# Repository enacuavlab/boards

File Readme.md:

# ENAC boards

This repository contains various resources related to ENAC's UAV team electronic boards, like hardware source files, and software templates.

## Tawaki

This is the lastest autopilot board based on a STMicroelectronics STM32F777VI.

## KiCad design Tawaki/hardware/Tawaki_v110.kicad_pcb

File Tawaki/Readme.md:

# Tawaki

This is the lastest autopilot board based on a STMicroelectronics STM32F777VI.

Find more details in the [Paparazzi UAV wiki](http://wiki.paparazziuav.org/wiki/Tawaki/v1.10).

+ **tawaki_chibios**: ChibiOS 20.3 basic example for Tawaki
+ **hardware**: electronic schematics and board KiCad files

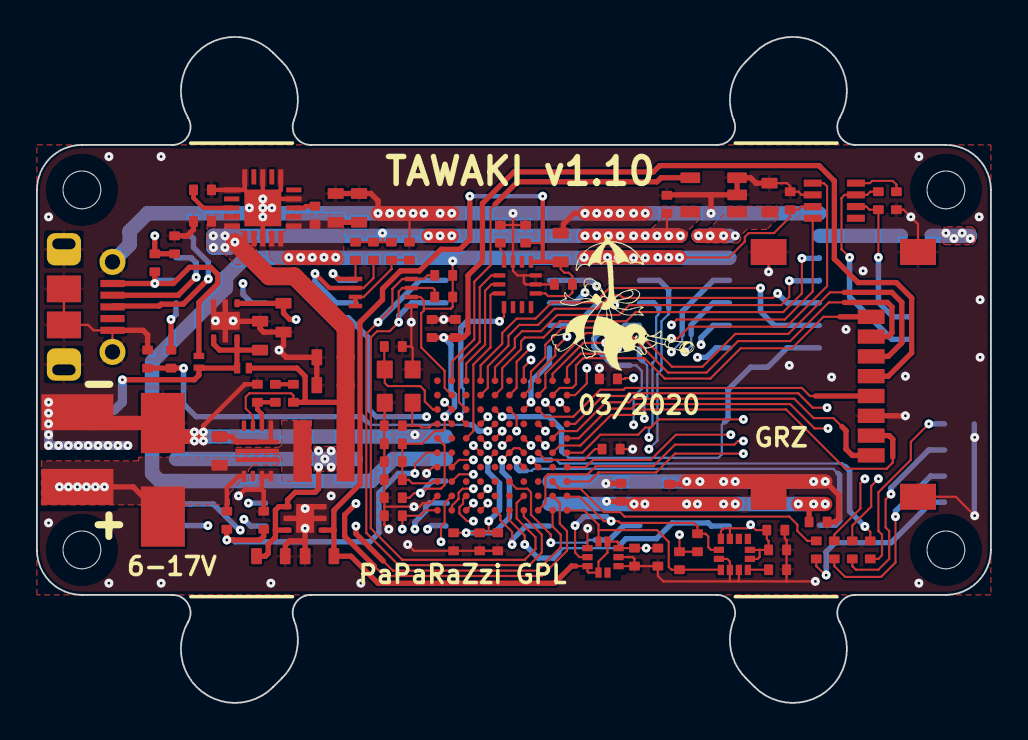
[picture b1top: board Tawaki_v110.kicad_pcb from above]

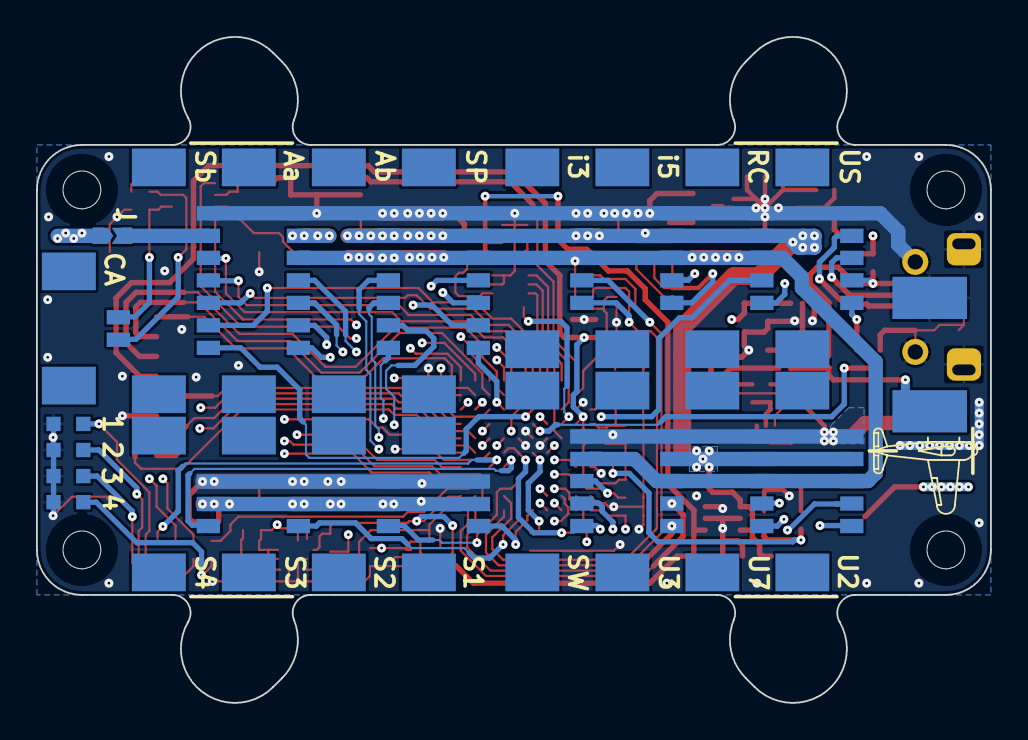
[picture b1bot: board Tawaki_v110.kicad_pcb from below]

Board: 4 copper layers, 53.0 x 37.0 mm, 107 parts (23 on the bottom side), 90 nets.

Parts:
C1, C2: 18pF; C_0402
C3, C4, C5, C6: 10nF; C_0402
C7, C8, C9, C10, C11, C12, C13, C14, C15, C16, C17, C18, C19, C20, C21, C22, C23, C24: 100nF; C_0402
C25, C26, C27, C28: 1µF; C_0402
C29: 1µF/25V/X5R; C_0603
C30, C31, C32: 4.7µF; C_0402
C33, C34, C35, C36, C37, C38, C39, C40, C41, C42: 10µF; C_0603
C43: 100µF/20V; EIA_7343-31
C44: 1000µF/6.3V; EIA_7360-38
D1, D2: PMEG3010AESB
IC1: TPS621351
IC2, IC3: LP5912-3.3DRV; LP5912DRV
IC4: TPS7A84ARGR
IC5: STM32F777VI
IC6: ICM-20600
IC7: LIS3MDL
IC8: BMP388
IC9: MAX3051EKA
IC10: PCA9306DCU
IC11: TPS2001DDBV
J1: CAN; PicoBlade_53398-0271
J2: SRVa1; PicoBlade_53398-0371
J3: SRVa2; PicoBlade_53398-0371
J4: SRVa3; PicoBlade_53398-0371
J5: SRVa4; PicoBlade_53398-0371
J6: SWD; PicoBlade_53398-0571
J7: RC; PicoBlade_53398-0571
J8: I2C-3V3; PicoBlade_53398-0571
J9: I2C-5V; PicoBlade_53398-0571
J10: UART2; PicoBlade_53398-0571
J11: UART3; PicoBlade_53398-0571
J12: UART7; PicoBlade_53398-0571
J13: USB; PicoBlade_53398-0571
J14: SRVb; PicoBlade_53398-0771
J15: AUXa; PicoBlade_53398-0771
J16: AUXb; PicoBlade_53398-0771
J17: SPI; PicoBlade_53398-0771
J18: USB_Micro-B; USB_Micro-B_Molex_105017-0001
J19: MicroSD_Connector_500901-0801; MicroSD_500901-0801
J20: +BAT; SquareWirePad_SMD_2x4mm
J21: GND; SquareWirePad_SMD_2x4mm
JP1: SolderJumper_2P; SolderJumper_2P_TrianglePads_0603
L1: 1µH; XFL4020
LED1: KP-1608SURC
LED2: KP-1608SEC
LED3: KP-1608CGCK
LED4: KP-1608SYC
Q1: 8Z_16MHz; Crystal_8Z
R1: 0Ω; R_0402
R2: 120Ω; R_0402
R3, R4, R5, R6: 390Ω; R_0402
R7, R8, R9: 1.5kΩ; R_0402
R10, R11, R12, R13, R14, R15, R16, R17, R18, R19: 2.2kΩ; R_0402
R20, R21: 12kΩ; R_0402
R22: 220kΩ; R_0402

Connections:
+3V3: C5.1, C22.2, C37.1, C38.1, IC4.1, IC4.2, IC4.19, IC4.20, IC5.B2, IC9.3, IC10.2, J6.2, J7.3, J8.3, J9.3, J10.3, J11.3, J12.3, J15.3, J16.3, J17.3, R13.1, R14.1
+3V3MCU: C12.1, C13.2, C14.2, C15.2, C18.2, C19.2, C26.2, C27.1, C31.2, C35.1, IC3.1, IC5.D2, IC5.F4, IC5.F5, IC5.F6, IC5.F7, IC5.H1, IC5.K1, J19.4
+3V3SENS: C3.2, C10.2, C11.1, C17.1, C24.2, C28.1, C40.1, C41.1, IC2.1, IC6.5, IC6.8, IC7.5, IC7.6, IC7.9, IC7.10, IC8.1, IC8.5, IC8.6, IC8.10, R11.1, R12.1
+5V: C9.1, C16.1, C20.1, C21.1, C25.1, C33.1, C39.1, C42.1, D1.2, IC1.6, IC2.4, IC2.6, IC4.14, IC4.15, IC4.16, IC4.17, IC11.5, J2.2, J3.2, J4.2, J5.2, J7.2, J8.2, J9.2, J10.2, J11.2, J12.2, J16.2, J17.2, L1.2, R15.1, R16.1, R21.2, R22.1
+5VAUX: C36.1, IC11.1, J15.2
+5VMCU: C34.1, C44.1, D1.1, D2.1, IC3.4, IC3.6
/APSW: IC5.A2, IC11.4
/AUXa1: IC5.G2, J15.4
/AUXa2: IC5.H2, J15.5
/AUXa3: IC5.J2, J15.6
/AUXa4: IC5.K2, J15.7
/AUXb1: IC5.J3, J16.4
/AUXb2: IC5.K3, J16.5
/AUXb3: IC5.J4, J16.6
/AUXb4: IC5.K4, J16.7
/BOOT: J13.5, R8.2
/BOOT0: IC5.D5, R8.1, R17.1
/CANH: IC9.7, J1.2, R2.1
/CANL: IC9.6, J1.1, R2.2
/CANRX: IC5.D8, IC9.4
/CANTX: IC5.E8, IC9.1
/DSHTin: IC5.C5, J14.7
/FB: IC1.5, R7.2, R10.1
/LED1: IC5.G8, R3.1
/LED2: IC5.D10, R4.1
/LED3: IC5.E10, R5.1
/LED4: IC5.H9, R6.1
/MISO2: IC5.H10, J17.6
/MISO4: IC5.D3, IC6.1
/MOSI2: IC5.G10, J17.5
/MOSI4: IC5.E3, IC6.14
/NSS2: IC5.K8, J17.4
/NSS4: IC5.C3, IC6.12
/OSCI: C2.2, IC5.C1, Q1.3
/OSCO: C1.2, IC5.D1, Q1.1
/RC1: IC5.D4, J7.4
/RC2: IC5.F10, J7.5
/RX2: IC5.C6, J10.4
/RX3: IC5.J9, J11.4
/RX7: IC5.A7, J12.4
/SCK2: IC5.C7, J17.7
/SCK4: IC5.A3, IC6.13
/SCL2: IC5.J7, IC10.3, J8.5, R14.2
/SCL2_5: IC10.6, J9.5, R16.2
/SCL4: IC5.K10, IC7.1, IC8.2, R12.2
/SD1ck: IC5.C8, J19.5
/SD1cmd: IC5.B7, J19.3
/SD1d0: IC5.F9, J19.7
/SD1d1: IC5.E9, J19.8
/SD1d2: IC5.B9, J19.1
/SD1d3: IC5.B8, J19.2
/SDA2: IC5.K7, IC10.4, J8.4, R13.2
/SDA2_5: IC10.5, J9.4, R15.2
/SDA4: IC5.J10, IC7.11, IC8.4, R11.2
/SRVa1: IC5.K5, J2.3
/SRVa2: IC5.H6, J3.3
/SRVa3: IC5.K6, J4.3
/SRVa4: IC5.G7, J5.3
/SRVb1: IC5.B5, J14.3
/SRVb2: IC5.A5, J14.4
/SRVb3: IC5.B4, J14.5
/SRVb4: IC5.A4, J14.6
/SW: IC1.2, L1.1
/SWCLK: IC5.A9, J6.4
/SWDIO: IC5.A10, J6.5
/TX2: IC5.B6, J10.5
/TX3: IC5.K9, J11.5
/TX7: IC5.A8, J12.5
/USB+: IC5.B10, J13.2, J18.3
/USB-: IC5.C10, J13.3, J18.2
/USBvbus: D2.2, J13.4, J18.1, R9.2
/USBvbus_LV: IC5.C9, R9.1, R19.1
/VBATmeas: IC5.F1, R18.1, R20.2
/VCAP1: C30.1, IC5.F8
/VCAP2: C32.1, IC5.E7
/nRST: C8.1, IC5.E1, J6.3
GND: C1.1, C2.1, C3.1, C4.2, C6.2, C7.2, C8.2, C9.2, C10.1, C11.2, C12.2, C13.1, C14.1, C15.1, C16.2, C17.2, C18.1, C19.1, C20.2, C21.2, C22.1, C23.2, C24.1, C25.2, C26.1, C27.2, C28.2, C29.2, C30.2, C31.1, C32.2, C33.2, C34.2, C35.2, C36.2, C37.2, C38.2, C39.2, C40.2, C41.2, C42.2, C43.2, C44.2, IC1.3, IC1.4, IC1.10, IC1.11, IC2.2, IC2.3, IC2.5, IC2.7, IC3.2, IC3.3, IC3.5, IC3.7, IC4.4, IC4.6, IC4.8, IC4.10, IC4.11, IC4.18, IC4.21, IC5.C2, IC5.E4, IC5.E5, IC5.E6, IC5.G1, IC5.J1, IC6.6, IC6.7, IC6.10, IC7.2, IC7.3, IC7.12, IC8.3, IC8.8, IC8.9, IC9.2, IC10.1, IC11.2, IC11.3, J2.1, J3.1, J4.1, J5.1, J6.1, J7.1, J8.1, J9.1, J10.1, J11.1, J12.1, J13.1, J14.1, J15.1, J16.1, J17.1, J18.5, J18.6, J19.6, J19.S, J21.1, LED1.1, LED2.1, LED3.1, LED4.1, Q1.2, Q1.4, R1.2, R10.2, R17.2, R18.2, R19.2
unnamed: C4.1, IC10.7, IC10.8, R22.2
unnamed: C5.2, IC4.3
unnamed: C6.1, IC4.13
unnamed: C7.1, IC7.4
unnamed: C23.1, IC6.11
unnamed: IC9.8, R1.1
unnamed: J14.2, JP1.2
unnamed: LED1.2, R3.2
unnamed: LED2.2, R4.2
unnamed: LED3.2, R5.2
unnamed: LED4.2, R6.2
unnamed: R7.1, R21.1
VBAT: C29.1, C43.1, IC1.1, IC1.8, J20.1, JP1.1, R20.1

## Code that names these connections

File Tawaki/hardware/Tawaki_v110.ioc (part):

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PD12.GPIO_Label=SCL4 (sensors)
PC7.GPIOParameters=GPIO_Label
PE11.GPIOParameters=GPIO_Label
PB10.Mode=I2C
PC12.Signal=SDMMC1_CK
PB14.GPIO_Label=MISO2 (pload)
PA14.GPIO_Label=SWCLK
PE9.GPIO_ModeDefaultPP=GPIO_MODE_AF_PP
PD3.GPIOParameters=GPIO_Label
PC6.GPIO_Label=RC2 (TX6)
PA3.GPIOParameters=GPIO_Label
PA6.GPIO_Label=AUXb1
PB6.GPIO_Label=SRVb1 (T4C1)
PD2.GPIOParameters=GPIO_Label
PD6.GPIO_Label=RX2
PA2.GPIOParameters=GPIO_Label
PE6.GPIO_Label=MOSI4 (IMU)
RCC.SYSCLKSource=RCC_SYSCLKSOURCE_PLLCLK
PD15.GPIOParameters=GPIO_Label
PE2.Mode=Full_Duplex_Slave
PD4.Signal=GPIO_Output
PB6.Signal=S_TIM4_CH1
PC7.Signal=GPIO_Output
PH1/OSC_OUT.Signal=RCC_OSC_OUT
PD8.Signal=USART3_TX
PE5.Signal=SPI4_MISO
PA1.GPIO_PuPd=GPIO_NOPULL
PB3.Mode=Asynchronous
PB12.GPIO_Label=nSS2
PB0.GPIOParameters=GPIO_Label
PE0.GPIOParameters=GPIO_Label
PA1.GPIOParameters=GPIO_Speed,GPIO_PuPd,GPIO_Label,GPIO_Mode
PE9.Signal=S_TIM1_CH1
PB14.Mode=Full_Duplex_Slave
PB1.GPIO_Label=AUXb4
PE4.GPIO_Label=nSS4 (IMU)
PC9.Mode=SD_4_bits_Wide_bus
PE2.Signal=SPI4_SCK
PD3.Mode=Full_Duplex_Slave
PC8.GPIOParameters=GPIO_Label
PB9.Signal=S_TIM4_CH4
Mcu.Package=TFBGA100
PB1.Signal=ADCx_IN9
PD12.Signal=I2C4_SCL
PD5.GPIOParameters=GPIO_Label
PA10.Signal=GPIO_Output
PC6.GPIO_PuPd=GPIO_NOPULL
PC11.Mode=SD_4_bits_Wide_bus
PB14.GPIOParameters=GPIO_Label
PB5.GPIO_Speed=GPIO_SPEED_FREQ_VERY_HIGH
PB10.GPIOParameters=GPIO_Label
PC6.GPIO_Speed=GPIO_SPEED_FREQ_VERY_HIGH
PD15.Signal=GPIO_Output
PA6.GPIOParameters=GPIO_Label
PD6.GPIOParameters=GPIO_Label
PA0/WKUP.GPIOParameters=GPIO_Speed,GPIO_PuPd,GPIO_Label,GPIO_Mode
PD9.GPIO_Label=RX3
PA15.GPIOParameters=GPIO_Label
PA1.GPIO_Mode=GPIO_MODE_AF_PP
PC13.Signal=GPIO_Output
PA9.GPIO_Label=USBvbus
PD3.Signal=SPI2_SCK
PC6.Signal=USART6_TX
PH1/OSC_OUT.GPIOParameters=GPIO_Label
PB11.GPIO_Label=SDA2 (pload)
PD13.GPIOParameters=GPIO_Label
PA11.GPIO_Label=USB-
PC11.GPIOParameters=GPIO_Label
PD6.Mode=Asynchronous
PD10.Signal=GPIO_Input
PB8.GPIO_Label=SRVb3 (T4C3)
PB11.Mode=I2C
PA9.Signal=USB_OTG_FS_VBUS
PB11.GPIOParameters=GPIO_Label
PE9.GPIO_Label=SRVa1 (T1C1)
PD8.Mode=Asynchronous
PA0/WKUP.Mode=CTS_RTS
PB10.Signal=I2C2_SCL
PB14.Signal=SPI2_MISO
PE13.GPIOParameters=GPIO_Label
PC12.Mode=SD_4_bits_Wide_bus
PE14.Signal=S_TIM1_CH4
PA1.Mode=CTS_RTS
PE6.Mode=Full_Duplex_Slave
PB15.GPIO_Label=MOSI2 (pload)
PA1.GPIO_Label=AUXa2
PA0/WKUP.GPIO_Label=AUXa1
PC10.GPIOParameters=GPIO_Label
PA0/WKUP.GPIO_PuPd=GPIO_NOPULL
PA13.Mode=Serial_Wire
PC9.GPIOParameters=GPIO_Label
PC7.GPIO_Label=LED3
PC8.Mode=SD_4_bits_Wide_bus
PB5.Signal=UART5_RX
PE13.GPIO_Label=SRVa3 (T1C3)
PD12.Mode=I2C
PA14.GPIOParameters=GPIO_Label
PB5.GPIO_PuPd=GPIO_NOPULL
PC12.GPIO_Label=SD1ck
PE5.GPIO_Label=MISO4 (IMU)
PA11.Signal=USB_OTG_FS_DM
PD2.Signal=SDMMC1_CMD
PB0.Signal=ADCx_IN8
PA7.GPIOParameters=GPIO_Label
PB12.GPIOParameters=GPIO_Label
PD2.GPIO_Label=SD1cmd
PH0/OSC_IN.GPIOParameters=GPIO_Label
Mcu.UserName=STM32F777VIHx
PD9.GPIOParameters=GPIO_Label
PE11.GPIO_Label=SRVa2 (T1C2)
PC10.Signal=SDMMC1_D2
PA12.GPIOParameters=GPIO_Label
PA9.GPIOParameters=GPIO_Label
PA11.GPIOParameters=GPIO_Label
PA11.Mode=Device_Only
PE9.GPIO_Speed=GPIO_SPEED_FREQ_LOW
PA0/WKUP.Signal=USART2_CTS
PB0.GPIO_Label=AUXb3
PC13.GPIO_Label=APSW
PB11.Signal=I2C2_SDA
PB15.Signal=SPI2_MOSI
PD9.Mode=Asynchronous
PE5.GPIOParameters=GPIO_Label
PB5.GPIOParameters=GPIO_ModeDefaultPP,GPIO_Speed,GPIO_PuPd,GPIO_Label
PD13.Signal=I2C4_SDA
PA15.GPIO_Label=TX7
PA12.Signal=USB_OTG_FS_DP
PE4.GPIOParameters=GPIO_Label
PC6.GPIO_ModeDefaultPP=GPIO_MODE_AF_PP
PH0/OSC_IN.Mode=HSE-External-Oscillator
PD8.GPIOParameters=GPIO_Label
PB5.GPIO_ModeDefaultPP=GPIO_MODE_AF_PP
PD5.Mode=Asynchronous
PD10.GPIOParameters=GPIO_Label
RCC.HSE_VALUE=16000000
PA15.Mode=Asynchronous
PH1/OSC_OUT.GPIO_Label=OSCO
PE13.Signal=S_TIM1_CH3
PA14.Mode=Serial_Wire
PC11.GPIO_Label=SD1d3
PA10.GPIO_Label=LED2
PB3.GPIOParameters=GPIO_Label
PA0/WKUP.GPIO_Speed=GPIO_SPEED_FREQ_VERY_HIGH
PB7.Signal=S_TIM4_CH2
PE4.Mode=NSS_Signal_Hard_Input
PH1/OSC_OUT.Mode=HSE-External-Oscillator
PE4.Signal=SPI4_NSS
PE6.GPIOParameters=GPIO_Label
PB6.GPIOParameters=GPIO_Label
PA13.GPIOParameters=GPIO_Label
PB7.GPIO_Label=SRVb2 (T4C2)
PD13.GPIO_Label=SDA4 (sensors)
PA6.Signal=S_TIM13_CH1
PB12.Mode=NSS_Signal_Hard_Input
PD5.GPIO_Label=TX2
PA2.GPIO_Label=AUXa3
PA15.Signal=UART7_TX
PA0/WKUP.GPIO_Mode=GPIO_MODE_AF_PP
PE0.GPIO_Label=RC1 (RX8)
PB5.GPIO_Label=DSHTin (RX5)
PD3.GPIO_Label=SCK2 (pload)
PD6.Signal=USART2_RX
PE2.GPIO_Label=SCK4 (IMU)
PA3.Signal=S_TIM9_CH2
PB3.GPIO_Label=RX7
PB8.GPIOParameters=GPIO_Label
PD15.GPIO_Label=LED1
PE14.GPIOParameters=GPIO_Label
PB9.GPIO_Label=SRVb4 (T4C4)
PC10.GPIO_Label=SD1d2
PC9.GPIO_Label=SD1d1
PC11.Signal=SDMMC1_D3
PC8.Signal=SDMMC1_D0
PC10.Mode=SD_4_bits_Wide_bus
PE14.GPIO_Label=SRVa4 (T1C4)
PD5.Signal=USART2_TX
PD9.Signal=USART3_RX
PA12.GPIO_Label=USB+
PB9.GPIOParameters=GPIO_Label
PE9.GPIOParameters=GPIO_ModeDefaultPP,GPIO_Speed,GPIO_PuPd,GPIO_Label
PD8.GPIO_Label=TX3
PC8.GPIO_Label=SD1d0
PC12.GPIOParameters=GPIO_Label
PA13.Signal=SYS_JTMS-SWDIO
PA9.Mode=Activate_VBUS
PD12.GPIOParameters=GPIO_Label
PB10.GPIO_Label=SCL2 (pload)
PB7.GPIOParameters=GPIO_Label
PD13.Mode=I2C
PE2.GPIOParameters=GPIO_Label
PD10.GPIO_Label=SDsw
PE11.Signal=S_TIM1_CH2
PA1.Signal=USART2_RTS
PD2.Mode=SD_4_bits_Wide_bus
board=custom
PB15.Mode=Full_Duplex_Slave
PH0/OSC_IN.Signal=RCC_OSC_IN
PC13.GPIOParameters=GPIO_Label
PD4.GPIO_Label=LED4
PA1.GPIO_Speed=GPIO_SPEED_FREQ_VERY_HIGH
PE5.Mode=Full_Duplex_Slave
PA10.GPIOParameters=GPIO_Label
PD4.GPIOParameters=GPIO_Label
PE6.Signal=SPI4_MOSI
PB15.GPIOParameters=GPIO_Label
PE0.Signal=UART8_RX
Mcu.Name=STM32F777VIHx
PA13.GPIO_Label=SWDIO
PA2.Signal=S_TIM9_CH1
PB3.Signal=UART7_RX
RCC.SYSCLKFreq_VALUE=216000000
PA7.GPIO_Label=AUXb2
PA12.Mode=Device_Only
PA14.Signal=SYS_JTCK-SWCLK
PC6.GPIOParameters=GPIO_ModeDefaultPP,GPIO_Speed,GPIO_PuPd,GPIO_Label
PH0/OSC_IN.GPIO_Label=OSCI
PB8.Signal=S_TIM4_CH3
PC9.Signal=SDMMC1_D1
PB12.Signal=SPI2_NSS
PA3.GPIO_Label=AUXa4
PB1.GPIOParameters=GPIO_Label
PA7.Signal=S_TIM14_CH1
PE9.GPIO_PuPd=GPIO_NOPULL

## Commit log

2021-02-25 Add Tawaki hardware and ChibiOS example.
2021-02-25 [Tawaki ChibiOS] Add gdb script.
2022-04-29 Add Chimera example.
2022-04-29 Update Tawaki debug conf for vscode.
2022-04-29 Add SVD file for Chimera.

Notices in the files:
Tawaki/hardware/Tawaki_v110.kicad_pcb:
PaPaRaZzi GPL
